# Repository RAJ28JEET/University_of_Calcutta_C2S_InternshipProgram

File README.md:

# University_of_Calcutta_C2S_InternshipProgram
Internship

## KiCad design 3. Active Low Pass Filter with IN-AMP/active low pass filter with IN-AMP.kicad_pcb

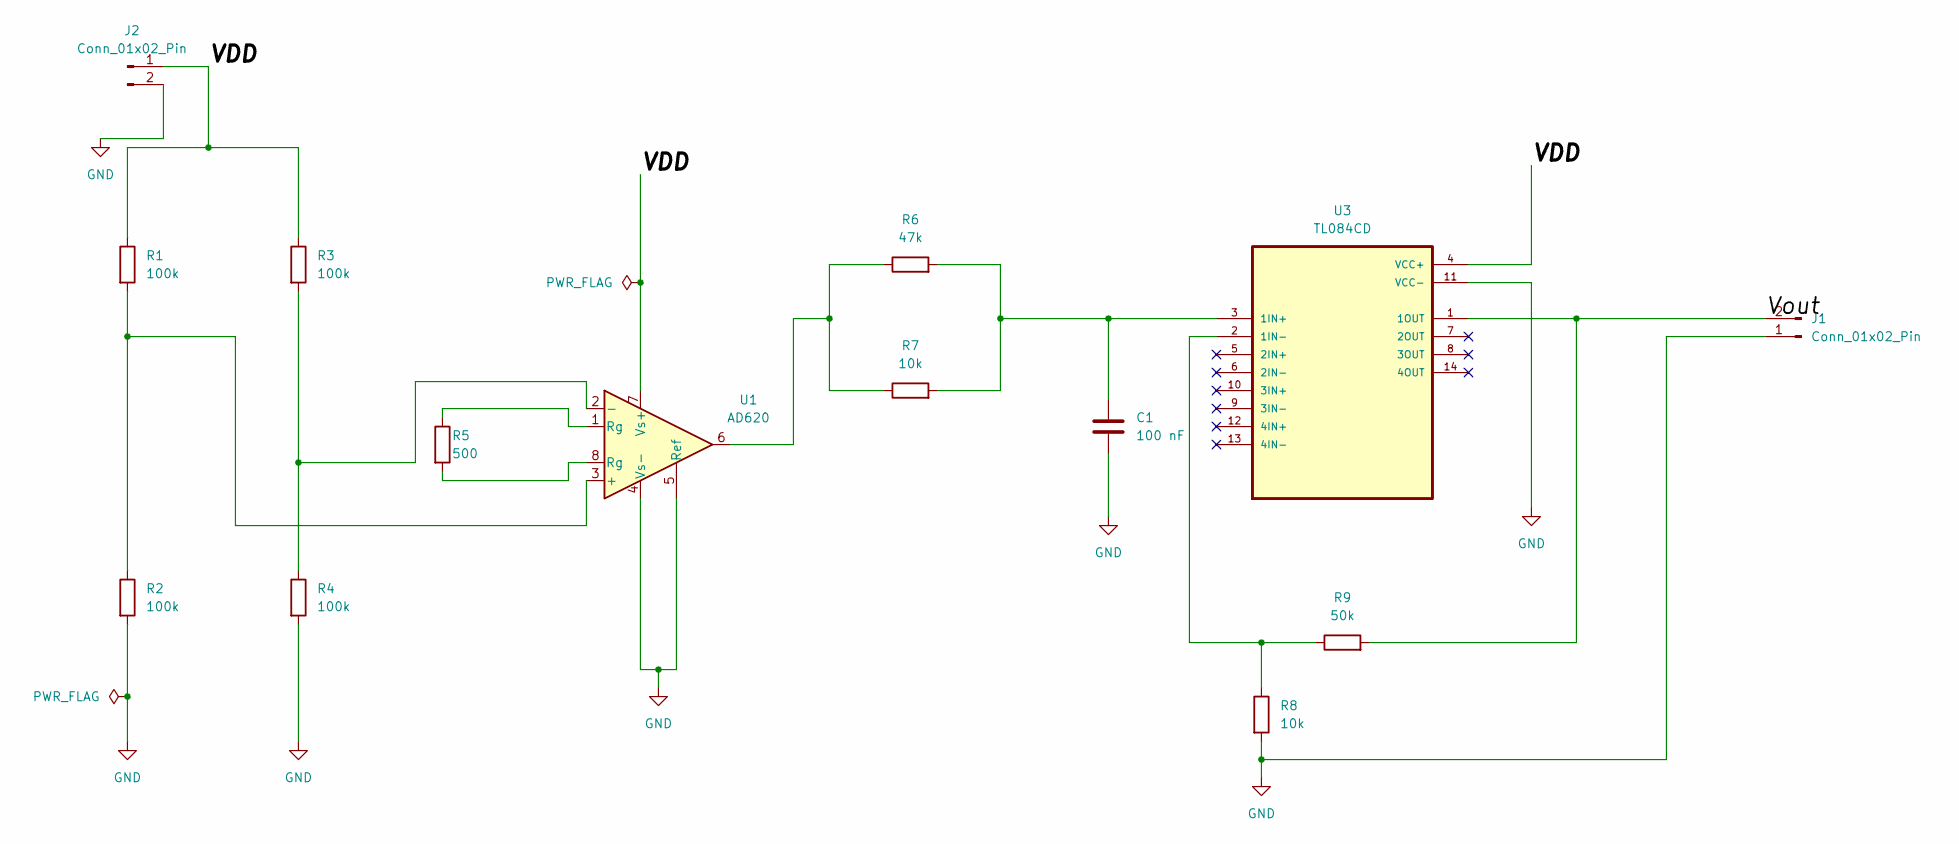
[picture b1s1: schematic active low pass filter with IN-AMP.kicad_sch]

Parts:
C1: 100 nF; C_Disc_D3.0mm_W1.6mm_P2.50mm
J1, J2: Conn_01x02_Pin; PinHeader_1x02_P2.54mm_Vertical
R1, R2, R3, R4: 100k; R_Axial_DIN0411_L9.9mm_D3.6mm_P12.70mm_Horizontal
R5: 500; R_Axial_DIN0411_L9.9mm_D3.6mm_P12.70mm_Horizontal
R6: 47k; R_Axial_DIN0411_L9.9mm_D3.6mm_P12.70mm_Horizontal
R7, R8: 10k; R_Axial_DIN0411_L9.9mm_D3.6mm_P12.70mm_Horizontal
R9: 50k; R_Axial_DIN0411_L9.9mm_D3.6mm_P12.70mm_Horizontal
U1: AD620; DIP787W46P254L1016H533Q8
U3: TL084CD; SOIC127P600X175-14N

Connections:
/VDD: J2.1, R1.1, R3.1, U1.7 (Vs+), U3.4 (VCC+)
/Vout: J1.2, R9.2, U3.1 (1OUT)
GND: C1.2, J1.1, J2.2, R2.2, R4.2, R8.2, U1.4 (Vs-), U1.5 (Ref), U3.11 (VCC-)
unnamed: R5.1, U1.1 (Rg)
unnamed: R5.2, U1.8 (Rg)
unnamed: R6.1, R7.1, U1.6
unnamed: R1.2, R2.1, U1.3 (+)
unnamed: R3.2, R4.1, U1.2 (-)
unnamed: C1.1, R6.2, R7.2, U3.3 (1IN+)
unnamed: R8.1, R9.1, U3.2 (1IN-)

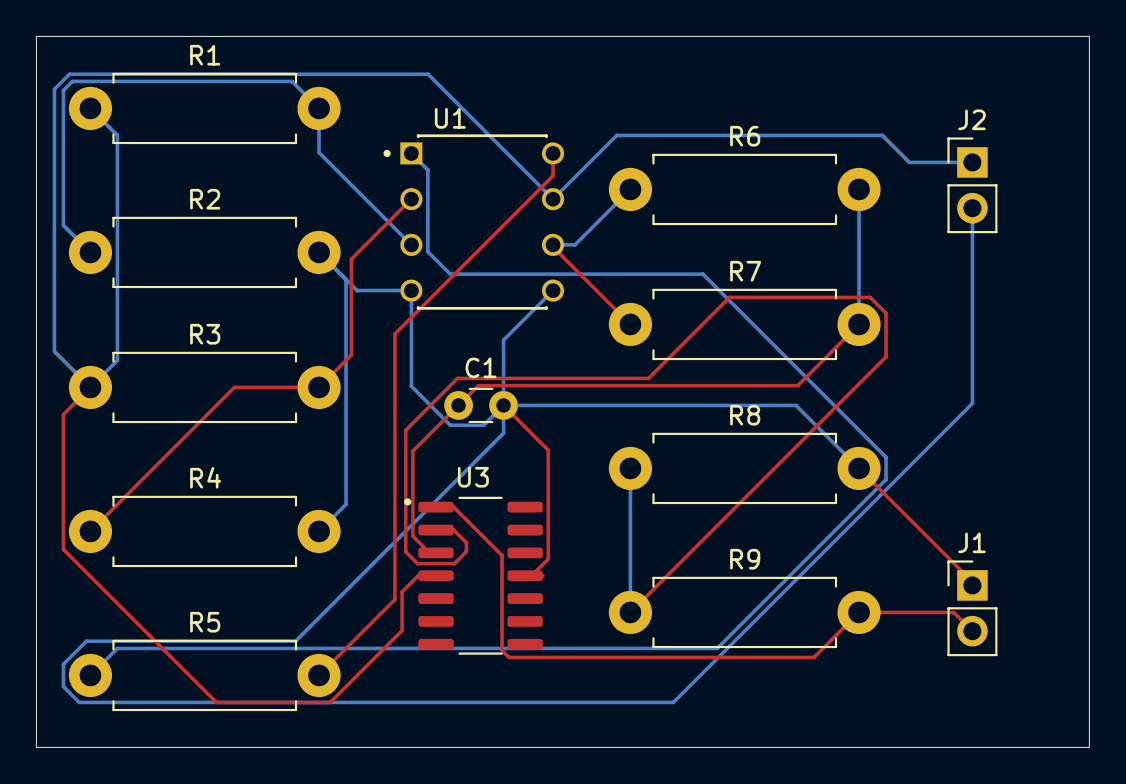
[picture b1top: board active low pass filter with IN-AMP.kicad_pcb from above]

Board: 2 copper layers, 58.5 x 39.5 mm, 14 parts (0 on the bottom side), 10 nets.

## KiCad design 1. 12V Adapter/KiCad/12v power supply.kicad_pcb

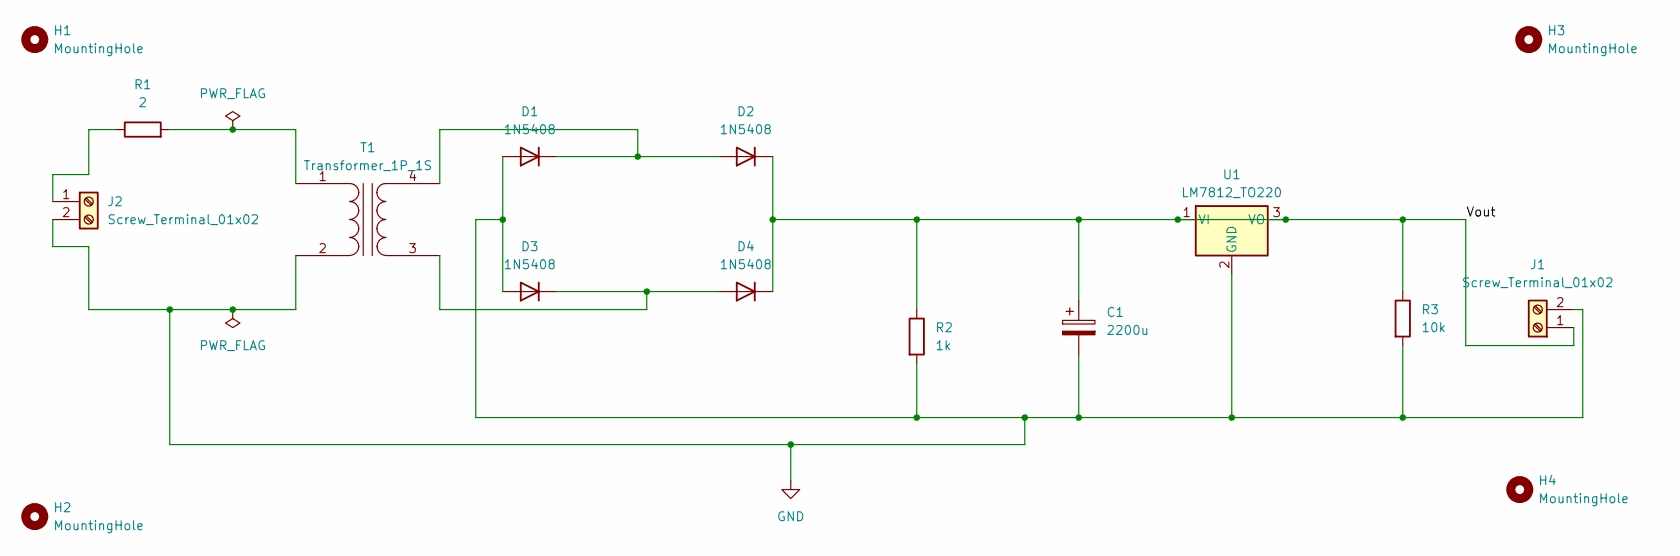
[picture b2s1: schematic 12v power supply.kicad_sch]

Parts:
C1: 2200u; CP_Radial_D8.0mm_P3.50mm
D1, D2, D3, D4: 1N5408; D_DO-201AD_P15.24mm_Horizontal
H1, H2, H3, H4: MountingHole; MountingHole_2.1mm
J1, J2: Screw_Terminal_01x02; TerminalBlock_bornier-2_P5.08mm
R1: 2; R_Axial_DIN0309_L9.0mm_D3.2mm_P12.70mm_Horizontal
R2: 1k; R_Axial_DIN0309_L9.0mm_D3.2mm_P12.70mm_Horizontal
R3: 10k; R_Axial_DIN0309_L9.0mm_D3.2mm_P12.70mm_Horizontal
T1: Transformer_1P_1S; Transformer_Coilcraft_CST1
U1: LM7812_TO220; TO-220-3_Vertical

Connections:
/Vout: C1.1, D2.1 (K), D4.1 (K), J1.1, R2.1, R3.1, U1.1 (VI), U1.3 (VO)
GND: C1.2, D1.2 (A), D3.2 (A), J1.2, J2.2, R2.2, R3.2, T1.2 (AB), U1.2 (GND)
unnamed: D1.1 (K), D2.2 (A), T1.4 (SB)
unnamed: D3.1 (K), D4.2 (A), T1.3 (SA)
unnamed: J2.1, R1.1
unnamed: R1.2, T1.1 (AA)

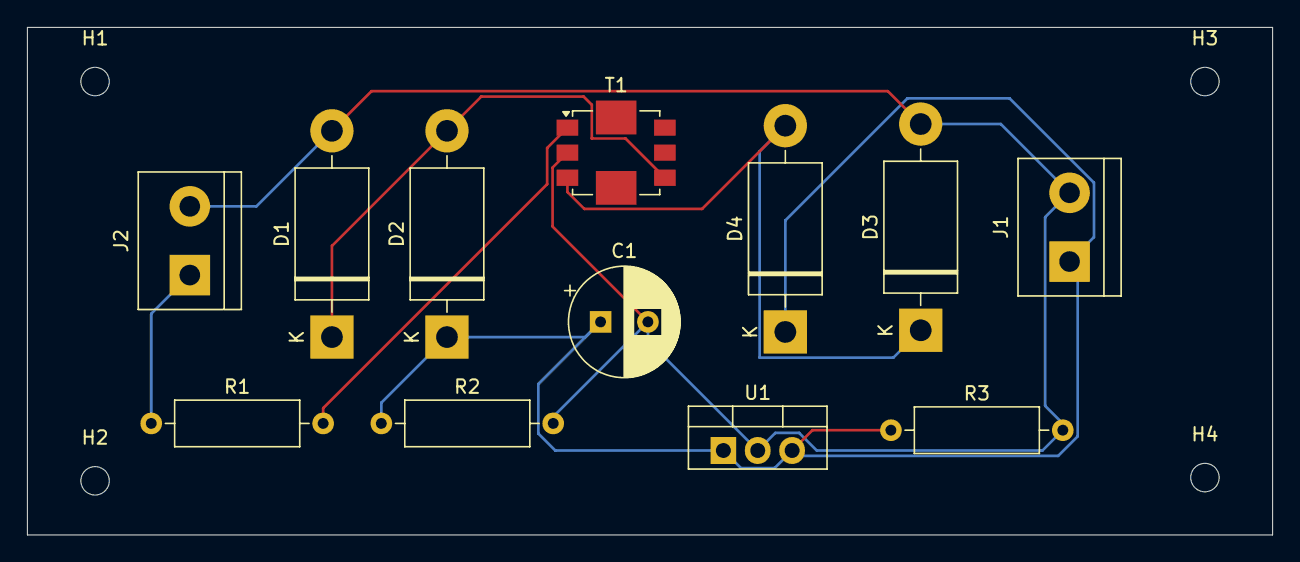
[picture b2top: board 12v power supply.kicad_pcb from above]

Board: 2 copper layers, 92.0 x 37.5 mm, 16 parts (0 on the bottom side), 6 nets.

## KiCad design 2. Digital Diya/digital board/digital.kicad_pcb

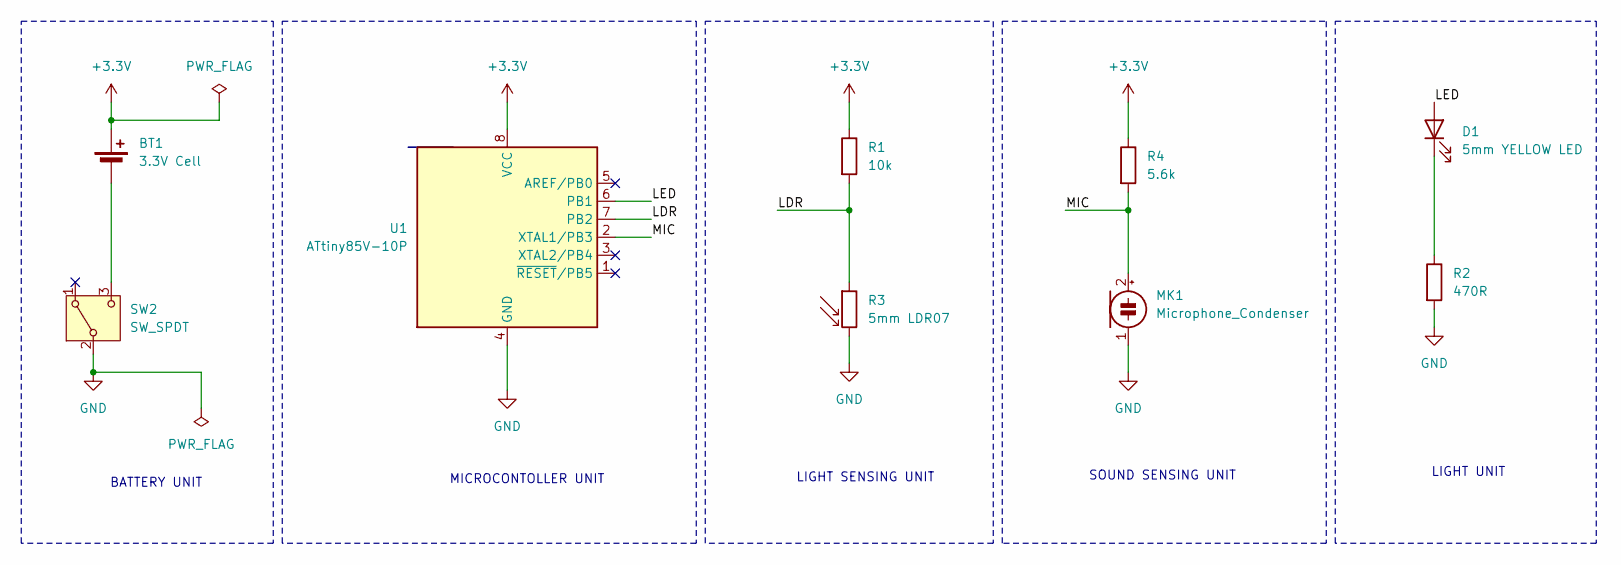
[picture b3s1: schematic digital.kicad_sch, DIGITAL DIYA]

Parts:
BT1: 3.3V Cell; BatteryHolder_ComfortableElectronic_CH273-2450_1x2450
D1: 5mm YELLOW LED; LED_D5.0mm
MK1: Microphone_Condenser; PinHeader_1x02_P2.54mm_Vertical
R1: 10k; R_Axial_DIN0207_L6.3mm_D2.5mm_P15.24mm_Horizontal
R2: 470R; R_Axial_DIN0207_L6.3mm_D2.5mm_P15.24mm_Horizontal
R3: 5mm LDR07; R_LDR_5.1x4.3mm_P3.4mm_Vertical
R4: 5.6k; R_Axial_DIN0207_L6.3mm_D2.5mm_P15.24mm_Horizontal
SW2: SW_SPDT; SW_Slide_SPDT_Angled_CK_OS102011MA1Q
U1: ATtiny85V-10P; DIP-8_W7.62mm

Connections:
+3.3V: BT1.1 (+), R1.1, R4.1, U1.8 (VCC)
/LDR: R1.2, R3.1, U1.7 (PB2)
/LED: D1.2 (A), U1.6 (PB1)
/MIC: MK1.2 (+), R4.2, U1.2 (XTAL1/PB3)
GND: MK1.1 (-), R2.2, R3.2, SW2.2 (B), U1.4 (GND)
unnamed: BT1.2 (-), SW2.3 (C)
unnamed: D1.1 (K), R2.1

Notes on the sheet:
LIGHT UNIT
SOUND SENSING UNIT
LIGHT SENSING UNIT
MICROCONTOLLER UNIT
BATTERY UNIT

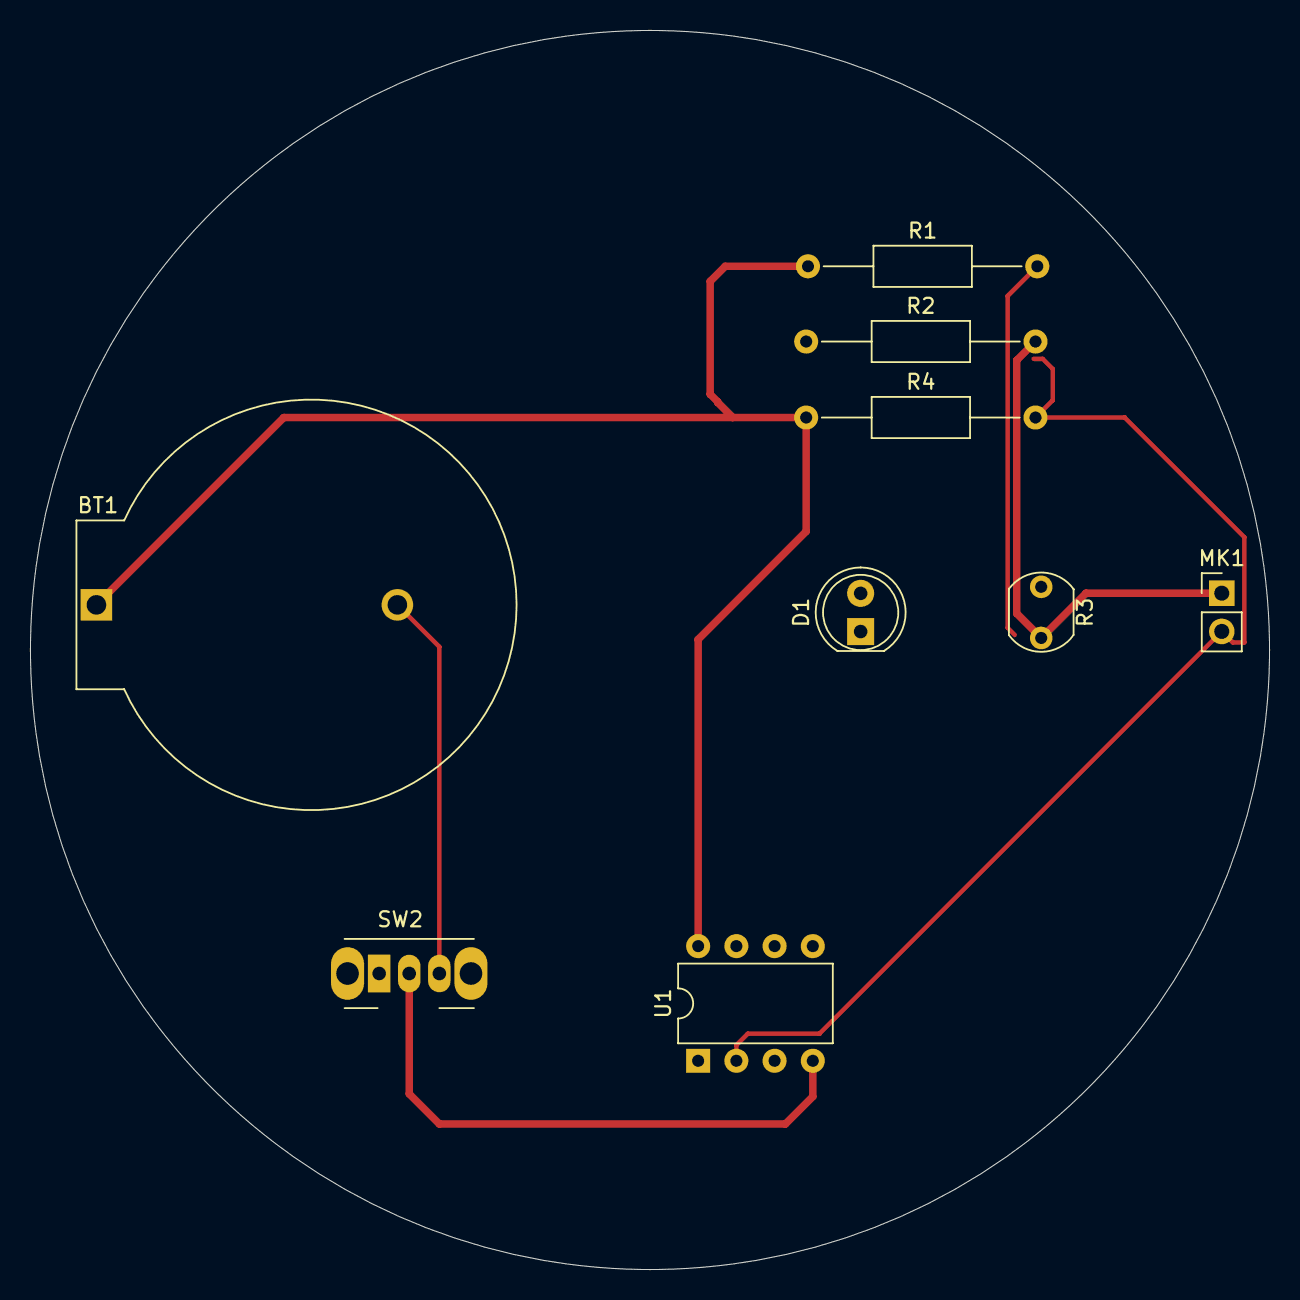
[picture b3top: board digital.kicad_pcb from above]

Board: 2 copper layers, 82.3 x 82.3 mm, 9 parts (0 on the bottom side), 7 nets.

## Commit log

2025-08-26 Lab Histroy
